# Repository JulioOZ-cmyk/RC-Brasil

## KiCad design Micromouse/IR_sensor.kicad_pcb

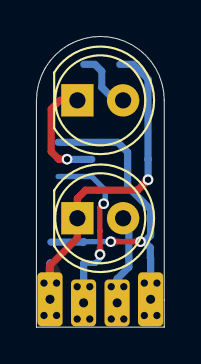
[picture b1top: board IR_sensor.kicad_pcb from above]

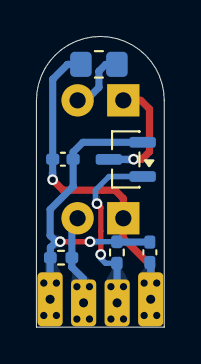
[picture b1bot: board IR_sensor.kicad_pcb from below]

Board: 2 copper layers, 7.1 x 16.1 mm, 9 parts (6 on the bottom side), 6 nets.

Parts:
C55: 10uF; C_0402_1005Metric_Pad0.74x0.62mm_HandSolder
C57: 0.1uF; C_0402_1005Metric_Pad0.74x0.62mm_HandSolder
D18: SFH-4550; LED_D5.0mm_Clear
J14: IR_1; IR_SENSOR_PAD_HIJO
Q4: AO3400A; SOT-23
Q6: ST-1KL3A; LED_D5.0mm_IRBlack
R39: 4.7k; R_0402_1005Metric_Pad0.72x0.64mm_HandSolder
R41: 20; R_0805_2012Metric_Pad1.20x1.40mm_HandSolder
R43: 3.3k; R_0402_1005Metric_Pad0.72x0.64mm_HandSolder

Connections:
/IR_sensor/+3V0_1: C55.1, C57.1, J14.1, Q6.1 (C), R41.2
/IR_sensor/GND_1: C55.2, C57.2, J14.4, Q4.2 (S), R39.2, R43.2
/IR_sensor/IR_POW_1: J14.2, Q4.1 (G), R39.1
/IR_sensor/IR_REC_1: J14.3, Q6.2 (E), R43.1
unnamed: D18.2 (A), R41.1
unnamed: D18.1 (K), Q4.3 (D)

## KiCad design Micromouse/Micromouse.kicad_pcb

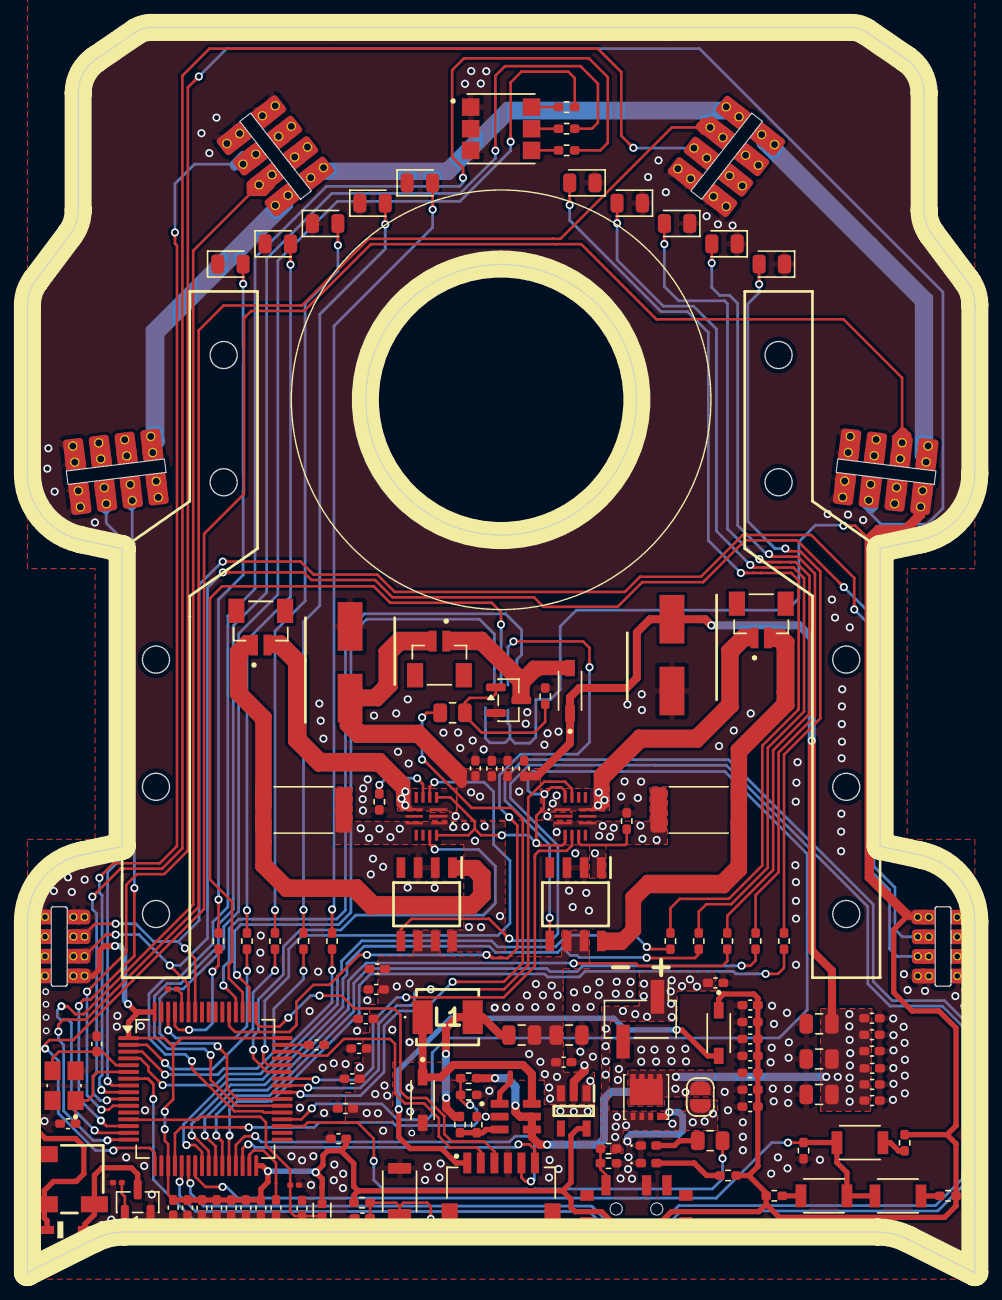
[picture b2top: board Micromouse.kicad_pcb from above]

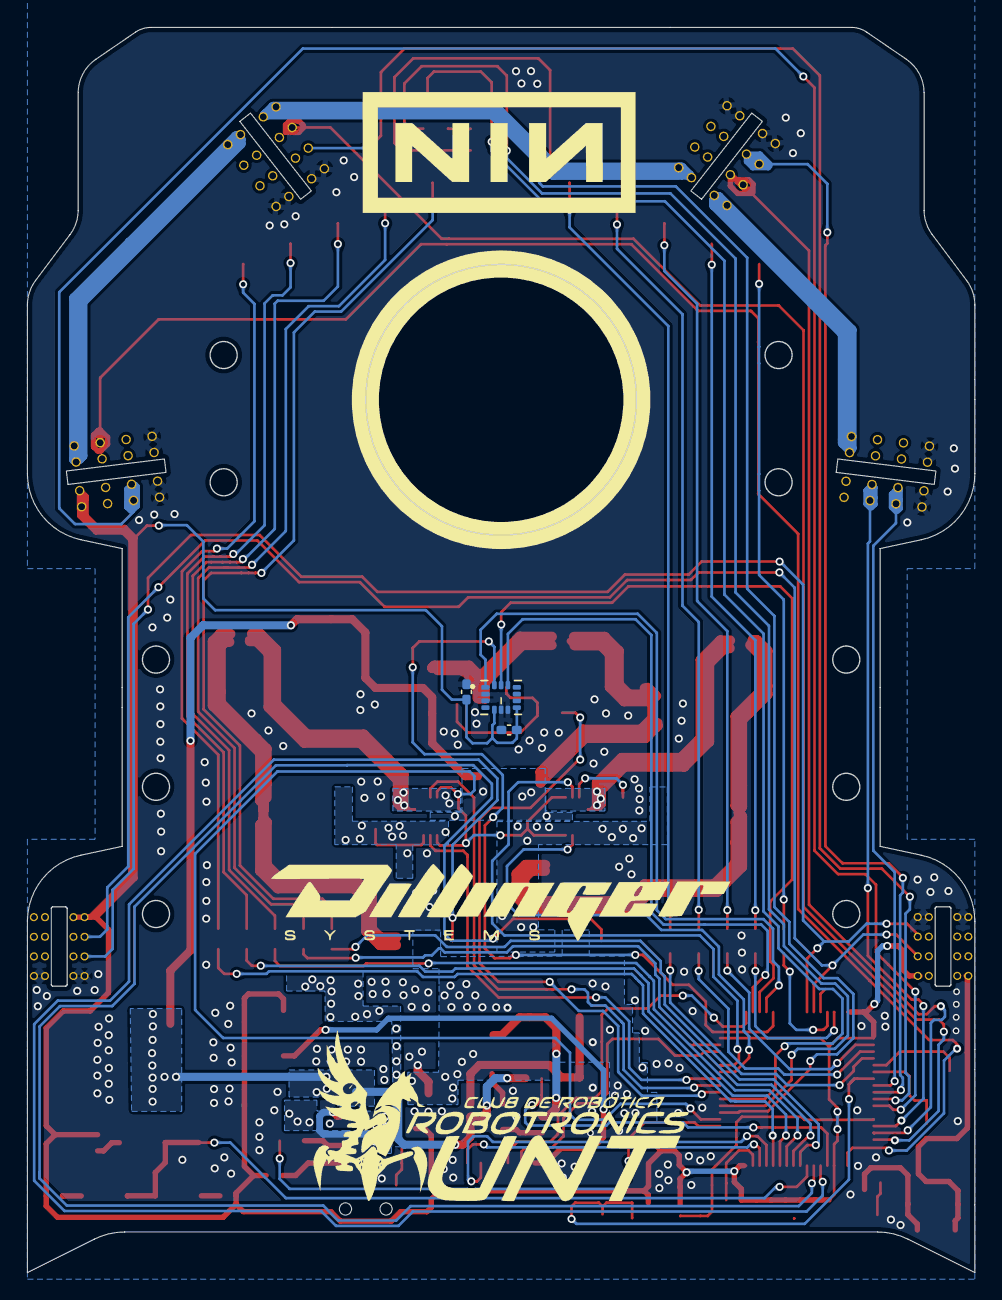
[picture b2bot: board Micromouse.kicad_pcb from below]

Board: 2 copper layers, 70.0 x 92.0 mm, 133 parts (3 on the bottom side), 90 nets.

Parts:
C1, C5, C7, C8, C9, C16, C20, C24, C29, C32, C35, C37, C42, C47, C48, C49, C52: 0.1uF; C_0402_1005Metric_Pad0.74x0.62mm_HandSolder
C2, C14, C31, C36: 1uF; C_0402_1005Metric_Pad0.74x0.62mm_HandSolder
C3, C4: 2.2uF; C_0402_1005Metric_Pad0.74x0.62mm_HandSolder
C6: 4.7uF; C_0402_1005Metric_Pad0.74x0.62mm_HandSolder
C10: 0.1uf; C_0402_1005Metric_Pad0.74x0.62mm_HandSolder
C11, C13, C28: 47uF; C_0805_2012Metric
C12, C23: 20pF; C_0402_1005Metric_Pad0.74x0.62mm_HandSolder
C15, C17, C18, C19, C21, C22, C25, C26, C30, C33, C34, C40, C50, C53: 10uF; C_0402_1005Metric_Pad0.74x0.62mm_HandSolder
C27, C38: 10nF; C_0201_0603Metric
C39, C41: 22uF; C_0805_2012Metric
C51, C54: APV0609471M010R; CAPAE660X980N
D1: 1N4148WS; SODFL2512X100N
D2, D10, D12: 1N5819HW-7; SOD3715X145N
D3, D4: LED; LED_0402_1005Metric_Pad0.77x0.64mm_HandSolder
D5, D6, D7, D8, D9, D13, D14, D15, D16, D17: LED; LED_0805_2012Metric
D11: LTST-G563ZEGBW; LED_LTST-G563ZEGBW
FB1: ACML-0402HC-121-T; BEADC1005X65N
J1: AS5048_Izq; ENCODER_PAD_PADRE
J2: AS5048_Der; ENCODER_PAD_PADRE
J3: MOT_FAN; JST_BM02B-SRSS-TB_LF__SN_
J4: IR_LAT_Der; IR_SENSOR_2
J5: IR_LAT_Izq; IR_SENSOR_2
J6: ST_LINK; JST_SM06B-SRSS-TB_LF__SN_
J7: IR_FRONT_Der; IR_SENSOR_2
J8: IR_FRONT_Izq; IR_SENSOR_2
J9: Lipo; PinHeader_1x02_P2.54mm_Vertical_SMD_Pin1Left
J12: MOT_I; JST_BM02B-SRSS-TB_LF__SN_
J13: MOT_D; JST_BM02B-SRSS-TB_LF__SN_
JP1: SolderJumper_2_Open; SolderJumper-2_P1.3mm_Open_RoundedPad1.0x1.5mm
L1: BMRA000404202R2MA1
LS1: Buzzer; CMT050203SMTTR
Q1, Q2: AO3400A; SOT-23
Q3: AON7423
R1, R5: 10k; R_0201_0603Metric
R2, R17: 47K; R_0402_1005Metric_Pad0.72x0.64mm_HandSolder
R3: 27K; R_0402_1005Metric_Pad0.72x0.64mm_HandSolder
R4: 220; R_0805_2012Metric
R6, R18, R35, R37: 10k; R_0402_1005Metric_Pad0.72x0.64mm_HandSolder
R7: 1K; R_0402_1005Metric_Pad0.72x0.64mm_HandSolder
R8: 10K; R_0402_1005Metric_Pad0.72x0.64mm_HandSolder
R9: 47k; R_0402_1005Metric_Pad0.72x0.64mm_HandSolder
R10: 330; R_0805_2012Metric
R11, R12, R13, R14, R15, R16, R19, R20, R21, R23, R24, R25, R26, R27: 330; R_0402_1005Metric_Pad0.72x0.64mm_HandSolder
R22: 51k; R_0402_1005Metric_Pad0.72x0.64mm_HandSolder
R28: 100K; R_0402_1005Metric_Pad0.72x0.64mm_HandSolder
R29: 33K; R_0402_1005Metric_Pad0.72x0.64mm_HandSolder
R30: 4.7K; R_0402_1005Metric_Pad0.72x0.64mm_HandSolder
R36, R38: 0.05; R_2512_6332Metric
S1: CUS-12TB; CUS-12B
S2: BTN_NRST; SW_B3U-1000PM
S3: BTN_1; SW_B3U-1000PM
S4: BTN_2; SW_B3U-1000PM
S5: BTN_3; SW_B3U-1000PM
U1: STM32F405RGTx; LQFP-64_10x10mm_P0.5mm
U2: MP2359DJ-LF-Z; SOT95P280X100-6N
U3: ME6211C30M5G; SOT95P282X145-5N
U6: LSM6DSRTR; PQFN50P250X300X86-14N
U7, U9: MP6551GQB-Z; MP6551GQBZ
U8, U10: AD8418AWHRZ; SOIC127P600X175-8N
Y1: 8MHz; XTAL_C3E-8.000-18-3030-R

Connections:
+3V0: C1.2, C2.2, C5.2, C6.2, C7.2, C8.2, C9.1, C14.1, C15.2, C16.1, C20.1, C24.1, C29.1, C33.1, C40.1, C47.2, C48.2, D1.C, D12.C, FB1.1, J1.1, J2.1, J4.1, J5.1, J7.1, J8.1, LS1.1 (+), R9.1, R16.1, R28.1, R29.1, R30.1, U1.1 (VBAT), U1.19 (VDD), U1.32 (VDD), U1.48 (VDD), U1.64 (VDD), U3.5 (VOUT), U6.5 (VDD_IO), U6.8 (VDD)
+3V3(ST-LINK): D12.A, J6.1
+5V: C10.1, C17.1, C21.1, C25.1, C30.1, C34.1, C39.2, C41.1, C42.1, U3.1 (VIN), U3.3 (CE), U8.6 (VS), U8.7 (VREF1), U10.6 (VS), U10.7 (VREF1)
/MP6551_Der/MOT_D+: J13.2, R38.2, U10.8 (+IN)
/MP6551_Der/MOT_D-: J13.1, U9.1 (OUT1_1), U9.10 (OUT1_2)
/MP6551_Der/SHUNT_MD: R38.1, U9.3 (OUT2_1), U9.8 (OUT2_2), U10.1 (-IN)
/MP6551_Izq/MOT_I+: J12.2, U7.3 (OUT2_1), U7.8 (OUT2_2)
/MP6551_Izq/MOT_I-: J12.1, R36.2, U8.1 (-IN)
/MP6551_Izq/SHUNT_MI: R36.1, U7.1 (OUT1_1), U7.10 (OUT1_2), U8.8 (+IN)
BAT_VOLTAGE: R2.2, R3.1, U1.20 (PA4)
BUZZER_OP: Q1.1 (G), R5.2
CS: U1.50 (PA15), U6.12 (CS)
CURRENT_MD: U1.21 (PA5), U10.5 (OUT)
CURRENT_MI: U1.22 (PA6), U8.5 (OUT)
ENABLE: U1.36 (PB15), U7.4 (EN2), U7.14 (EN1), U9.4 (EN2), U9.14 (EN1)
GND: C1.1, C2.1, C3.2, C4.2, C5.1, C6.1, C7.1, C8.1, C9.2, C10.2, C11.1, C12.2, C13.1, C14.2, C15.1, C16.2, C17.2, C18.1, C19.1, C20.2, C21.2, C22.1, C23.2, C24.2, C25.2, C26.1, C27.2, C28.1, C29.2, C30.2, C31.2, C32.1, C33.2, C34.2, C35.1, C36.2, C37.2, C40.2, C41.2, C42.2, C47.1, C48.1, C49.1, C50.1, C51.2 (-), C52.1, C53.1, C54.2 (-), D3.1 (K), D4.1 (K), D5.1 (K), D6.1 (K), D7.1 (K), D8.1 (K), D9.1 (K), D10.A, D11.1, D11.2, D11.3, D13.1 (K), D14.1 (K), D15.1 (K), D16.1 (K), D17.1 (K), J1.4, J2.4, J4.4, J5.4, J6.4, J7.4, J8.4, J9.2, Q1.2 (S), Q2.2 (S), Q3.4 (G), R1.1, R3.2, R5.1, R6.1, R7.2, R17.1, R18.2, R35.1, R37.1, S1.P$2 (2), S2.2, U1.12 (VSSA), U1.18 (VSS), U1.63 (VSS), U2.2 (GND), U3.2 (VSS), U6.2 (SDX), U6.3 (SCX), U6.6 (GND), U6.7 (GND), U7.9 (GND), U8.2 (GND), U8.3 (VREF2), U9.9 (GND), U10.2 (GND), U10.3 (VREF2), Y1.2 (GND), Y1.4 (GND)
IN1_Der: U1.41 (PA8), U9.13 (IN1)
IN1_Izq: U1.43 (PA10), U7.13 (IN1)
IN2_Der: U1.42 (PA9), U9.5 (IN2)
IN2_Izq: U1.44 (PA11), U7.5 (IN2)
IR_POW_1: J4.2, U1.15 (PA1)
IR_POW_2: J5.2, U1.16 (PA2)
IR_POW_3: J7.2, U1.17 (PA3)
IR_POW_4: J8.2, U1.14 (PA0)
IR_REC_1: J4.3, U1.9 (PC1)
IR_REC_2: J5.3, U1.10 (PC2)
IR_REC_3: J7.3, U1.11 (PC3)
IR_REC_4: J8.3, U1.8 (PC0)
LED_1: R11.1, U1.24 (PC4)
LED_2: R12.1, U1.25 (PC5)
LED_3: R13.1, U1.26 (PB0)
LED_4: R14.1, U1.27 (PB1)
LED_5: R15.1, U1.28 (PB2)
LED_6: R23.1, U1.61 (PB8)
LED_7: R24.1, U1.62 (PB9)
LED_8: R25.1, U1.2 (PC13)
LED_9: R26.1, U1.3 (PC14)
LED_10: R27.1, U1.4 (PC15)
LED_B: R21.1, U1.39 (PC8)
LED_ESTADO: R10.1, U1.35 (PB14)
LED_G: R20.1, U1.38 (PC7)
LED_R: R19.1, U1.37 (PC6)
LIPO: C36.1, J9.1, JP1.2 (B), Q3.1 (S_1), Q3.2 (S_2), Q3.3 (S_3), R8.2
MENU_ESTADO: R17.2, S3.1, S4.1, S5.1, U1.23 (PA7)
MISO: U1.52 (PC11), U6.1 (SDO/SA0)
MOSI: U1.53 (PC12), U6.14 (SDA)
NRST: C37.1, R9.2, S2.1, U1.7 (NRST)
unnamed: C39.1, L1.2, R22.2
unnamed: D3.2 (A), R10.2
unnamed: D4.2 (A), R16.2
unnamed: D5.2 (A), R11.2
unnamed: D6.2 (A), R12.2
unnamed: D7.2 (A), R13.2
unnamed: D8.2 (A), R14.2
unnamed: D9.2 (A), R15.2
unnamed: D11.4, R19.2
unnamed: D11.5, R20.2
unnamed: D11.6, R21.2
unnamed: D13.2 (A), R23.2
unnamed: D14.2 (A), R24.2
unnamed: D15.2 (A), R25.2
unnamed: D16.2 (A), R26.2
unnamed: D17.2 (A), R27.2
unnamed: D1.A, LS1.2 (-), Q1.3 (D)
unnamed: D2.A, J3.1, Q2.3 (D)
unnamed: Q2.1 (G), R4.1, R6.2
unnamed: R28.2, S3.2
unnamed: R29.2, S4.2
unnamed: R30.2, S5.2
unnamed: R7.1, R8.1, S1.P$1 (1)
unnamed: R1.2, U1.60 (BOOT0)
unnamed: C3.1, U1.31 (VCAP_1)
unnamed: C4.1, U1.47 (VCAP_2)
unnamed: C38.1, U2.1 (BST)
unnamed: R18.1, R22.1, U2.3 (FB)
unnamed: C38.2, D10.C, L1.1, U2.6 (SW)
unnamed: R35.2, U7.6 (SR)
unnamed: R37.2, U9.6 (SR)
POW_IN: C11.2, C13.2, C18.2, C19.2, C22.2, C26.2, C28.2, C32.2, C35.2, C49.2, C50.2, C51.1 (+), C52.2, C53.2, C54.1 (+), D2.C, J3.2, JP1.1 (A), Q3.5 (D_1), Q3.6 (D_2), Q3.7 (D_3), Q3.8 (D_4), Q3.9 (D_5), R2.1, U2.4 (EN), U2.5 (IN), U7.2 (VIN), U9.2 (VIN)
PWM_FAN: R4.2, U1.40 (PC9)
RCC_OSC_IN: C23.1, U1.5 (PH0), Y1.3
RCC_OSC_OUT: C12.1, U1.6 (PH1), Y1.1
RX: J6.6, U1.30 (PB11)
SCL: U1.51 (PC10), U6.13 (SCL)
SCL_s: J1.3, J2.3, U1.58 (PB6)
SDA_s: J1.2, J2.2, U1.59 (PB7)
SYS_JTCK-SWCLK: J6.3, U1.49 (PA14)
SYS_JTMS-SWDIO: J6.2, U1.46 (PA13)
TX: J6.5, U1.29 (PB10)
VDDA: C27.1, C31.1, FB1.2, U1.13 (VDDA)

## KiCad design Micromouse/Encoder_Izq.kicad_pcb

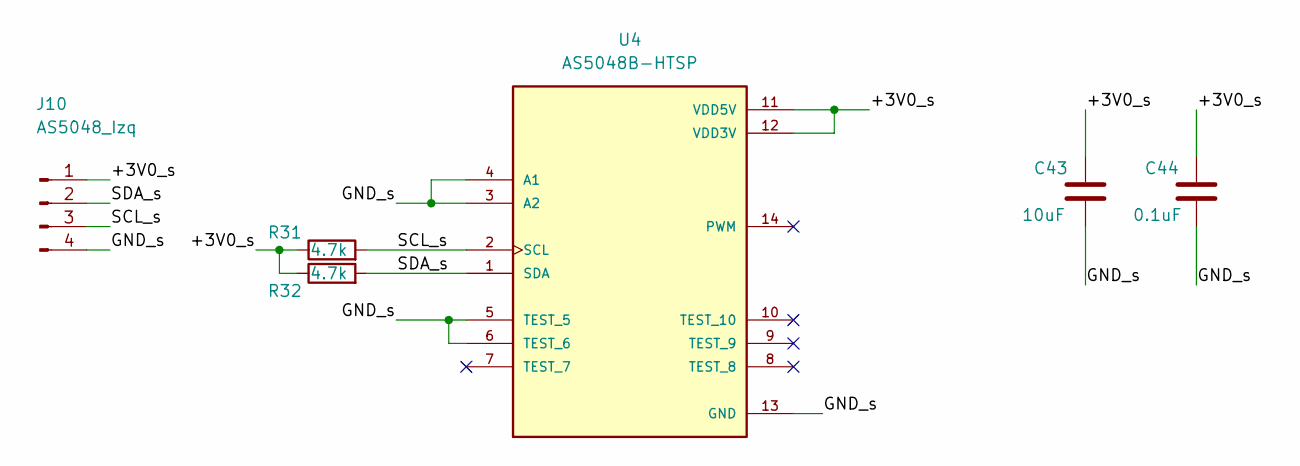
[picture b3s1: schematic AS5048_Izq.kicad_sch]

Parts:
C43: 10uF; C_0402_1005Metric
C44: 0.1uF; C_0402_1005Metric
J10: AS5048_Izq; Encoder1
R31, R32: 4.7k; R_0402_1005Metric
U4: AS5048B-HTSP; SOP65P640X120-14N; PARTREV 1-11

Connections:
/AS5048_Izq/+3V0_s: C43.1, C44.1, J10.1, R31.1, R32.1, U4.11 (VDD5V), U4.12 (VDD3V)
/AS5048_Izq/GND_s: C43.2, C44.2, J10.4, U4.3 (A2), U4.4 (A1), U4.5 (TEST_5), U4.6 (TEST_6), U4.13 (GND)
/AS5048_Izq/SCL_s: J10.3, R31.2, U4.2 (SCL)
/AS5048_Izq/SDA_s: J10.2, R32.2, U4.1 (SDA)

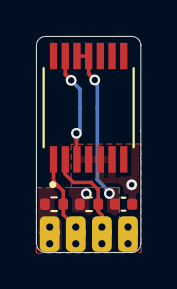
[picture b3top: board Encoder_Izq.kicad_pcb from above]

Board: 2 copper layers, 5.8 x 12.0 mm, 6 parts (1 on the bottom side), 4 nets.

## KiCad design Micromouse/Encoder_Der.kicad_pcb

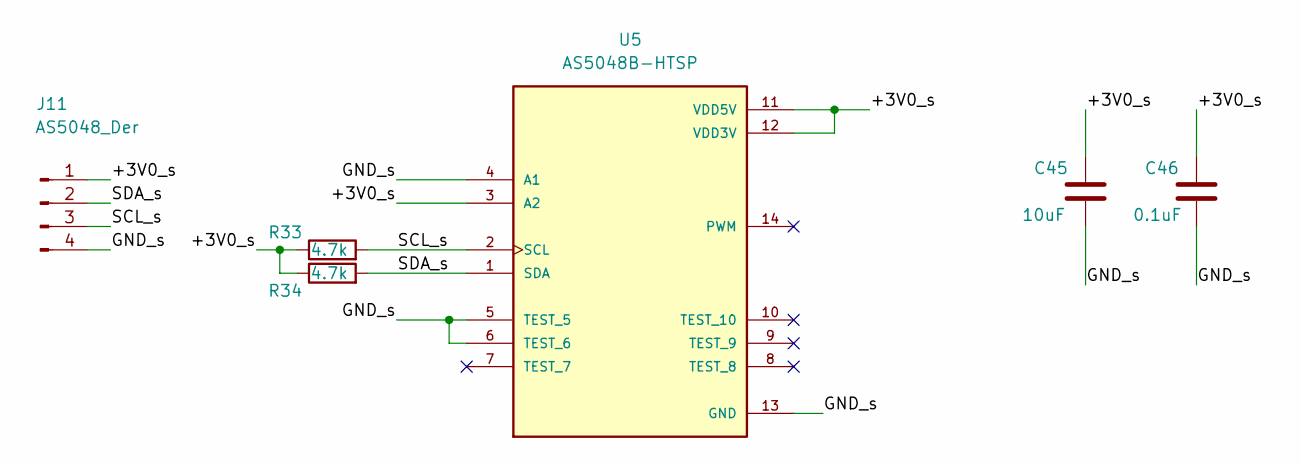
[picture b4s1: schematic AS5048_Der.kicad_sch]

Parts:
C45: 10uF; C_0402_1005Metric
C46: 0.1uF; C_0402_1005Metric
J11: AS5048_Der; Encoder1
R33, R34: 4.7k; R_0402_1005Metric
U5: AS5048B-HTSP; SOP65P640X120-14N; PARTREV 1-11

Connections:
/AS5048_Der/+3V0_s: C45.1, C46.1, J11.1, R33.1, R34.1, U5.3 (A2), U5.11 (VDD5V), U5.12 (VDD3V)
/AS5048_Der/GND_s: C45.2, C46.2, J11.4, U5.4 (A1), U5.5 (TEST_5), U5.6 (TEST_6), U5.13 (GND)
/AS5048_Der/SCL_s: J11.3, R33.2, U5.2 (SCL)
/AS5048_Der/SDA_s: J11.2, R34.2, U5.1 (SDA)

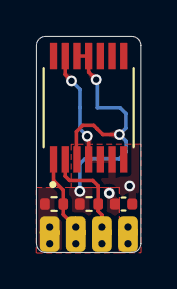
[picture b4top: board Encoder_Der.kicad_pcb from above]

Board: 2 copper layers, 5.8 x 12.0 mm, 6 parts (1 on the bottom side), 4 nets.

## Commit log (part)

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2026-03-24 Estructura corregida
2026-03-24 Commit de prueba
2026-03-24 Prueba 1
2026-03-24 Archivo de texto de prueba
2026-03-24 Eliminacion de archivo de texto de prueba
2026-03-24 Cambios hechos en gitignore
2026-03-24 Cambios en gitignore
2026-03-26 Añadiendo el chasis de minisumo
2026-03-31 Commit4
2026-03-31 Esquematico corregido
2026-03-31 Esquematico corregido del micromouse
2026-06-15 Chasis minisumo terminado
2026-06-19 Red 3V0 cambiada a 3V3
2026-06-28 Modelos 3D agregados
2026-06-28 STL de prueba
2026-06-28 STL de prueba eliminado
